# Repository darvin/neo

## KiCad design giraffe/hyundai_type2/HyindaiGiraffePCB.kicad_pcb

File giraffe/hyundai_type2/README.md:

# Hyuindai Giraffe type 2

This Giraffe is not really Giraffe, it doesnt connect to Panda via OBD port - instead, it replaces the OBD board.

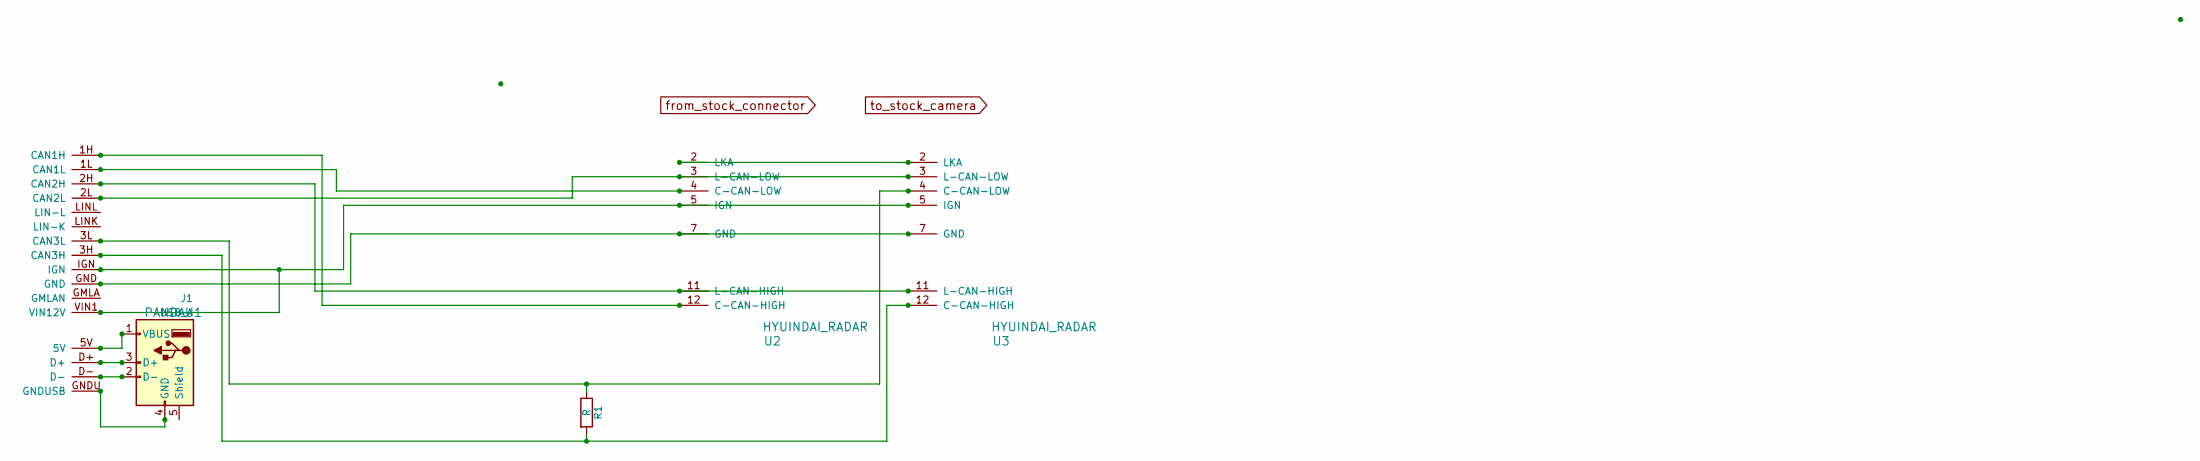
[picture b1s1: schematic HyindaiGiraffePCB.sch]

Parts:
J1: USB_A
R1: R; Resistor_SMD+THTuniversal_0805to1206_RM10_HandSoldering
U1: PANDA; PANDA_PINOUT
U2: HYUINDAI_RADAR; MG645845
U3: HYUINDAI_RADAR; RadarWires

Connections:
unnamed: J1.1 (VBUS), U1.5V
unnamed: J1.2 (D-), U1.D-
unnamed: J1.3 (D+), U1.D+
unnamed: J1.4 (GND), U1.GNDU (GNDUSB)
unnamed: R1.1, U1.3L (CAN3L), U3.4 (C-CAN-LOW)
unnamed: R1.2, U1.3H (CAN3H), U3.12 (C-CAN-HIGH)
unnamed: U1.1H (CAN1H), U2.12 (C-CAN-HIGH)
unnamed: U1.1L (CAN1L), U2.4 (C-CAN-LOW)
unnamed: U1.2H (CAN2H), U2.11 (L-CAN-HIGH), U3.11 (L-CAN-HIGH)
unnamed: U1.2L (CAN2L), U2.3 (L-CAN-LOW), U3.3 (L-CAN-LOW)
unnamed: U1.GND, U2.7 (GND), U3.7 (GND)
unnamed: U1.IGN, U1.VIN1 (VIN12V), U2.5 (IGN), U3.5 (IGN)
unnamed: U2.2 (LKA), U3.2 (LKA)

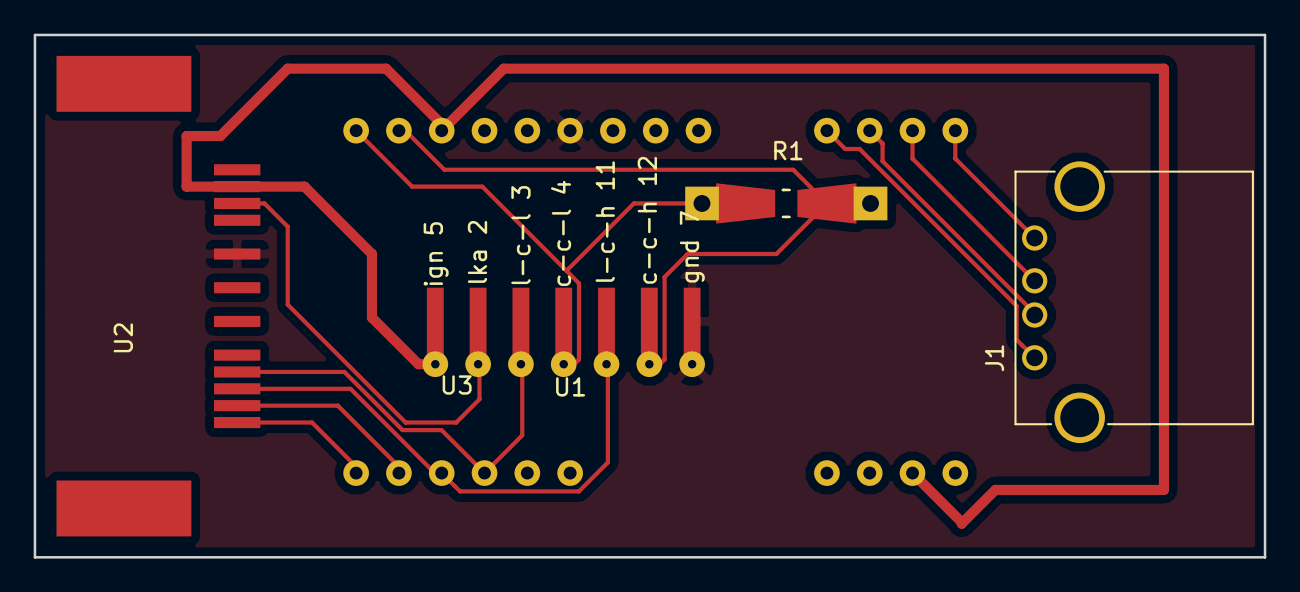
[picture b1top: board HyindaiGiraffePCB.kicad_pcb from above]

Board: 2 copper layers, 73.0 x 31.0 mm, 5 parts (0 on the bottom side), 13 nets.

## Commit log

2019-02-18 added hyundai giraffe type 2
